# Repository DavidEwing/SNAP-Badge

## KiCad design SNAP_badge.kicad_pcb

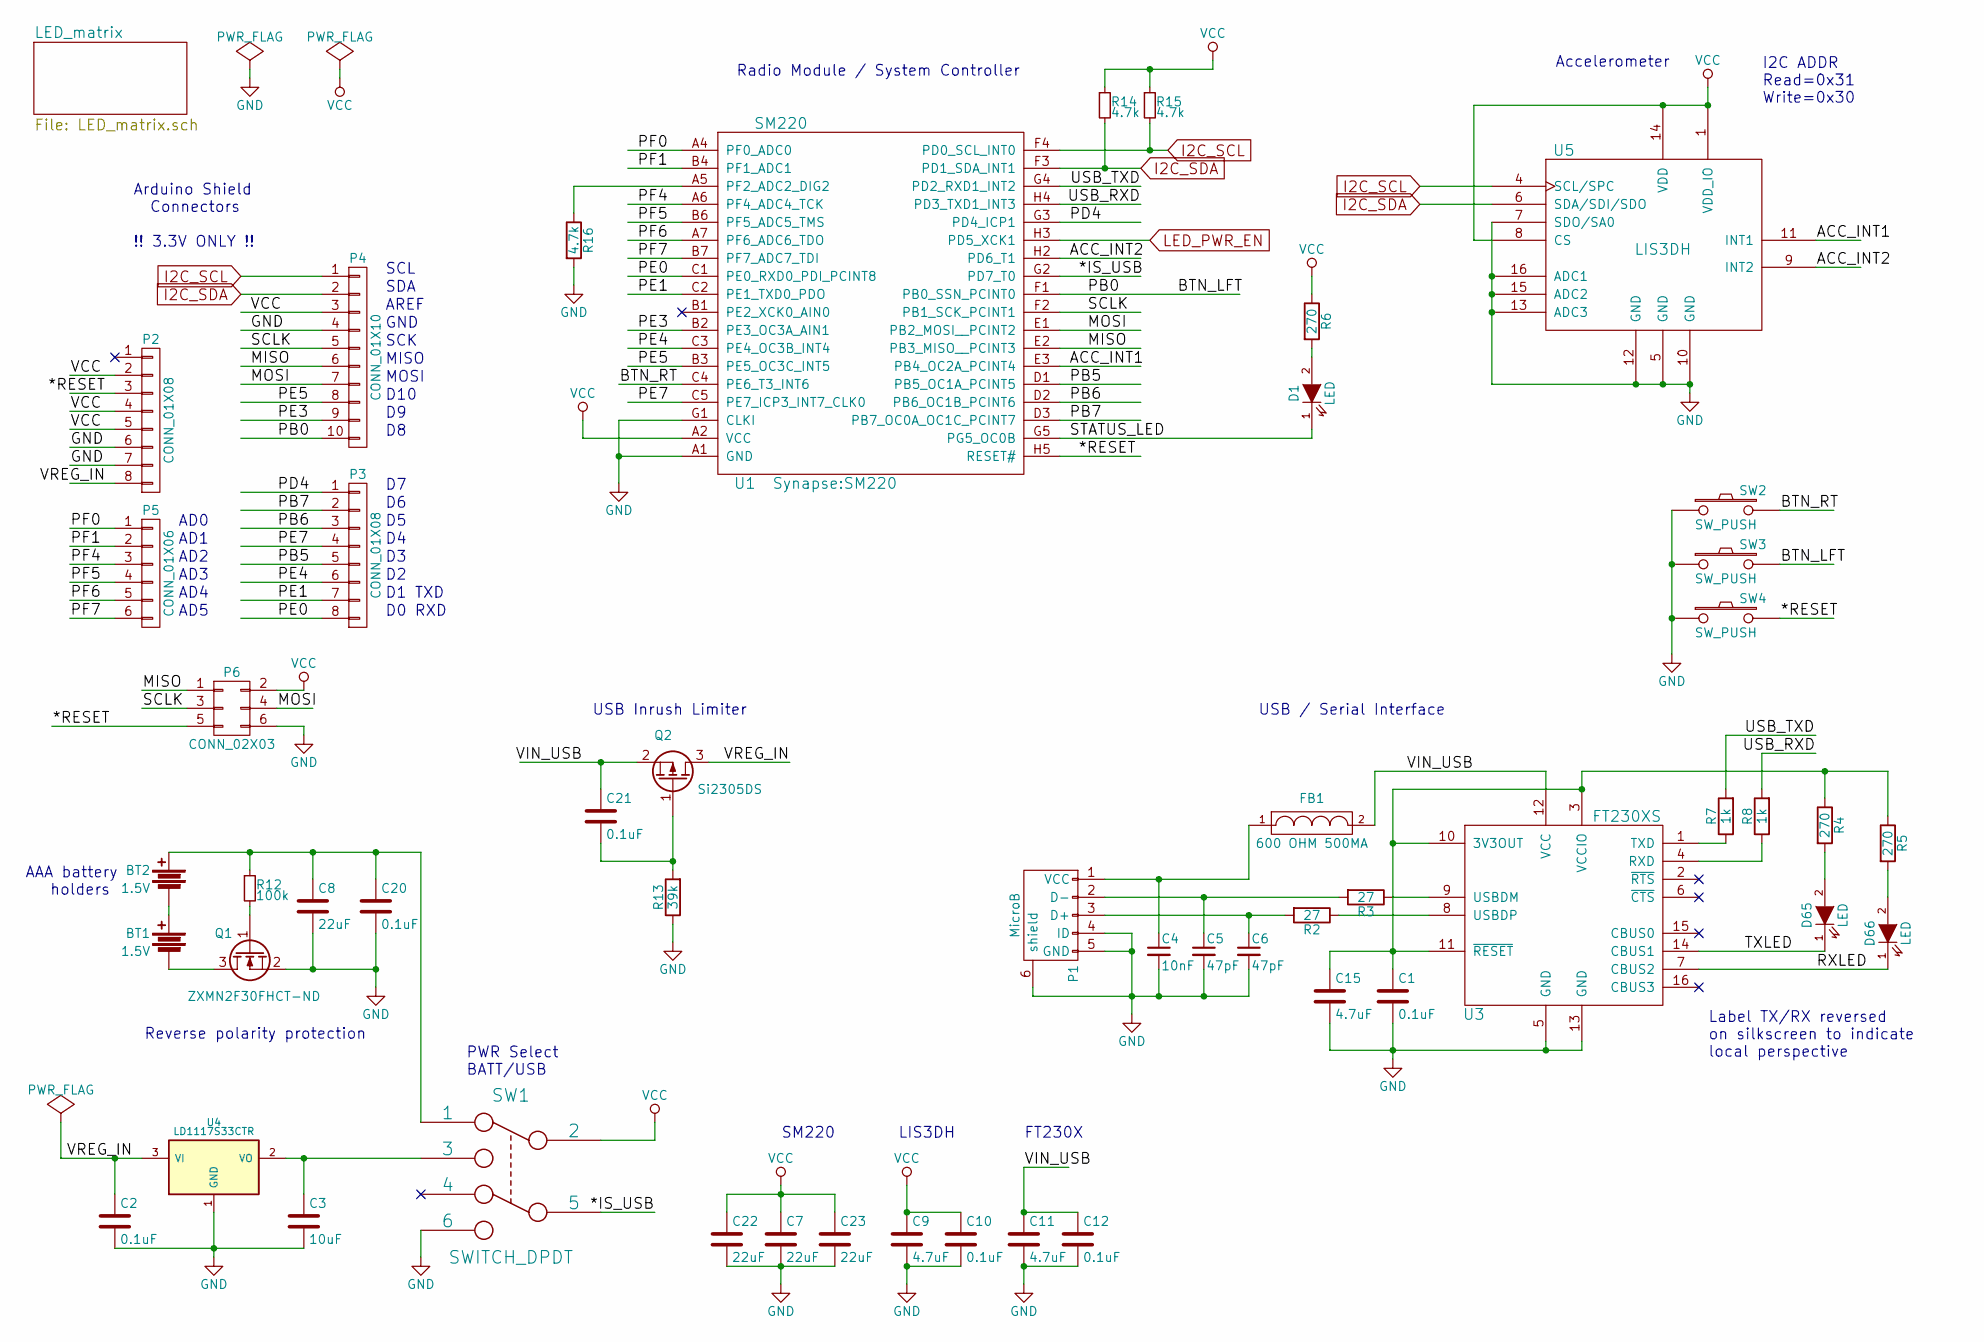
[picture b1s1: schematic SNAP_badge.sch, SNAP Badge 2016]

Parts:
BT1, BT2: 1.5V; BATT_2466
C1, C2, C10, C12, C20, C21: 0.1uF; C_0603
C3: 10uF; C_0603
C4: 10nF; C_0603
C5, C6: 47pF; C_0603
C7, C8, C22, C23: 22uF; C_0603
C9, C11, C15: 4.7uF; C_0603
D1, D65, D66: LED; Led_0603
FB1: 600 OHM 500MA; R_0603
P1: MicroB; USBmicroB
P2, P3: CONN_01X08; Socket_Strip_Straight_1x08
P4: CONN_01X10; Socket_Strip_Straight_1x10
P5: CONN_01X06; Socket_Strip_Straight_1x06
P6: CONN_02X03; Pin_Header_Straight_2x03
Q1: ZXMN2F30FHCT-ND; SOT-23
Q2: Si2305DS; SOT-23
R2, R3: 27; R_0603
R4, R5, R6: 270; R_0603
R7, R8: 1k; R_0603
R12: 100k; R_0603
R13: 39k; R_0603
R14, R15, R16: 4.7k; R_0603
SW1: SWITCH_DPDT; SO-DPDT-6
SW2, SW3, SW4: SW_PUSH; SW_SPST_PTS645
U1: SM220
U3: FT230XS; SSOP-16_3.9x4.9mm_Pitch0.635mm
U4: LD1117S33CTR; SOT-223
U5: LIS3DH; LGA16_3x3

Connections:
/*IS_USB: SW1.5, U1.G2 (PD7_T0)
/*RESET: P2.3, P6.5, SW4.2, U1.H5 (RESET#)
/ACC_INT1: U1.E3 (PB4_OC2A_PCINT4), U5.11 (INT1)
/ACC_INT2: U1.H2 (PD6_T1), U5.9 (INT2)
/BTN_LFT: P4.10, SW3.2, U1.F1 (PB0_SSN_PCINT0)
/BTN_RT: SW2.2, U1.C4 (PE6_T3_INT6)
/MISO: P4.6, P6.1, U1.E2 (PB3_MISO__PCINT3)
/MOSI: P4.7, P6.4, U1.E1 (PB2_MOSI__PCINT2)
/PB5: P3.5, U1.D1 (PB5_OC1A_PCINT5)
/PB6: P3.3, U1.D2 (PB6_OC1B_PCINT6)
/PB7: P3.2, U1.D3 (PB7_OC0A_OC1C_PCINT7)
/PD4: P3.1, U1.G3 (PD4_ICP1)
/PE0: P3.8, U1.C1 (PE0_RXD0_PDI_PCINT8)
/PE1: P3.7, U1.C2 (PE1_TXD0_PDO)
/PE3: P4.9, U1.B2 (PE3_OC3A_AIN1)
/PE4: P3.6, U1.C3 (PE4_OC3B_INT4)
/PE5: P4.8, U1.B3 (PE5_OC3C_INT5)
/PE7: P3.4, U1.C5 (PE7_ICP3_INT7_CLK0)
/PF0: P5.1, U1.A4 (PF0_ADC0)
/PF1: P5.2, U1.B4 (PF1_ADC1)
/PF4: P5.3, U1.A6 (PF4_ADC4_TCK)
/PF5: P5.4, U1.B6 (PF5_ADC5_TMS)
/PF6: P5.5, U1.A7 (PF6_ADC6_TDO)
/PF7: P5.6, U1.B7 (PF7_ADC7_TDI)
/RXLED: D66.1 (K), U3.7 (CBUS2)
/SCLK: P4.5, P6.3, U1.F2 (PB1_SCK_PCINT1)
/STATUS_LED: D1.1 (K), U1.G5 (PG5_OC0B)
/TXLED: D65.1 (K), U3.14 (CBUS1)
/USB_RXD: R8.2, U1.H4 (PD3_TXD1_INT3)
/USB_TXD: R7.2, U1.G4 (PD2_RXD1_INT2)
/VIN_USB: C11.1, C12.1, C21.1, FB1.2, Q2.2 (S), U3.12 (VCC)
/VREG_IN: C2.1, P2.8, Q2.3 (D), U4.3 (VI)
GND: C1.2, C2.2, C3.2, C4.2, C5.2, C6.2, C7.2, C8.2, C9.2, C10.2, C11.2, C12.2, C15.2, C20.2, C22.2, C23.2, P1.4 (ID), P1.5 (GND), P1.6 (shield), P2.6, P2.7, P4.4, P6.6, Q1.2 (S), R13.1, R16.2, SW1.6, SW2.1, SW3.1, SW4.1, U1.A1 (GND), U1.A8 (GND), U1.B8 (GND), U1.D8 (GND), U1.F8 (GND), U1.G1 (CLKI), U1.G8 (GND), U1.H1 (GND), U1.H8 (GND), U3.5 (GND), U3.13 (GND), U4.1 (GND), U5.5 (GND), U5.7 (SDO/SA0), U5.10 (GND), U5.12 (GND), U5.13 (ADC3), U5.15 (ADC2), U5.16 (ADC1); also elsewhere on the board
I2C_SCL: P4.1, R15.2, U1.F4 (PD0_SCL_INT0), U5.4 (SCL/SPC); also elsewhere on the board
I2C_SDA: P4.2, R14.2, U1.F3 (PD1_SDA_INT1), U5.6 (SDA/SDI/SDO); also elsewhere on the board
LED_PWR_EN: U1.H3 (PD5_XCK1); also elsewhere on the board
unnamed: BT1.1, BT2.2
unnamed: BT1.2, Q1.3 (D)
unnamed: BT2.1, C8.1, C20.1, R12.1, SW1.1
unnamed: C1.1, C15.1, R4.1, R5.1, U3.3 (VCCIO), U3.10 (3V3OUT), U3.11 (~RESET)
unnamed: C3.1, SW1.3, U4.2 (VO)
unnamed: C4.1, FB1.1, P1.1 (VCC)
unnamed: C5.1, P1.2 (D-), R3.2
unnamed: C6.1, P1.3 (D+), R2.2
unnamed: C21.2, Q2.1 (G), R13.2
unnamed: D1.2 (A), R6.2
unnamed: D65.2 (A), R4.2
unnamed: D66.2 (A), R5.2
unnamed: Q1.1 (G), R12.2
unnamed: R2.1, U3.8 (USBDP)
unnamed: R3.1, U3.9 (USBDM)
unnamed: R7.1, U3.1 (TXD)
unnamed: R8.1, U3.4 (RXD)
unnamed: R16.1, U1.A5 (PF2_ADC2_DIG2)
VCC: C7.1, C9.1, C10.1, C22.1, C23.1, P2.2, P2.4, P2.5, P4.3, P6.2, R6.1, R14.1, R15.1, SW1.2, U1.A2 (VCC), U1.A3 (VCC), U5.1 (VDD_IO), U5.8 (CS), U5.14 (VDD); also elsewhere on the board

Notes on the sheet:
Reverse polarity protection
PWR Select BATT/USB
I2C ADDR Read=0x31 Write=0x30
Accelerometer
USB / Serial Interface
Radio Module / System Controller
SM220
LIS3DH
FT230X
AD0
AD1
AD2
AD3
AD4
AD5
SCL
SDA
AREF
GND
SCK
MISO
MOSI
D10
D1 TXD
D0 RXD
Arduino Shield Connectors !! 3.3V ONLY !!
AAA battery holders
USB Inrush Limiter
Label TX/RX reversed on silkscreen to indicate local perspective

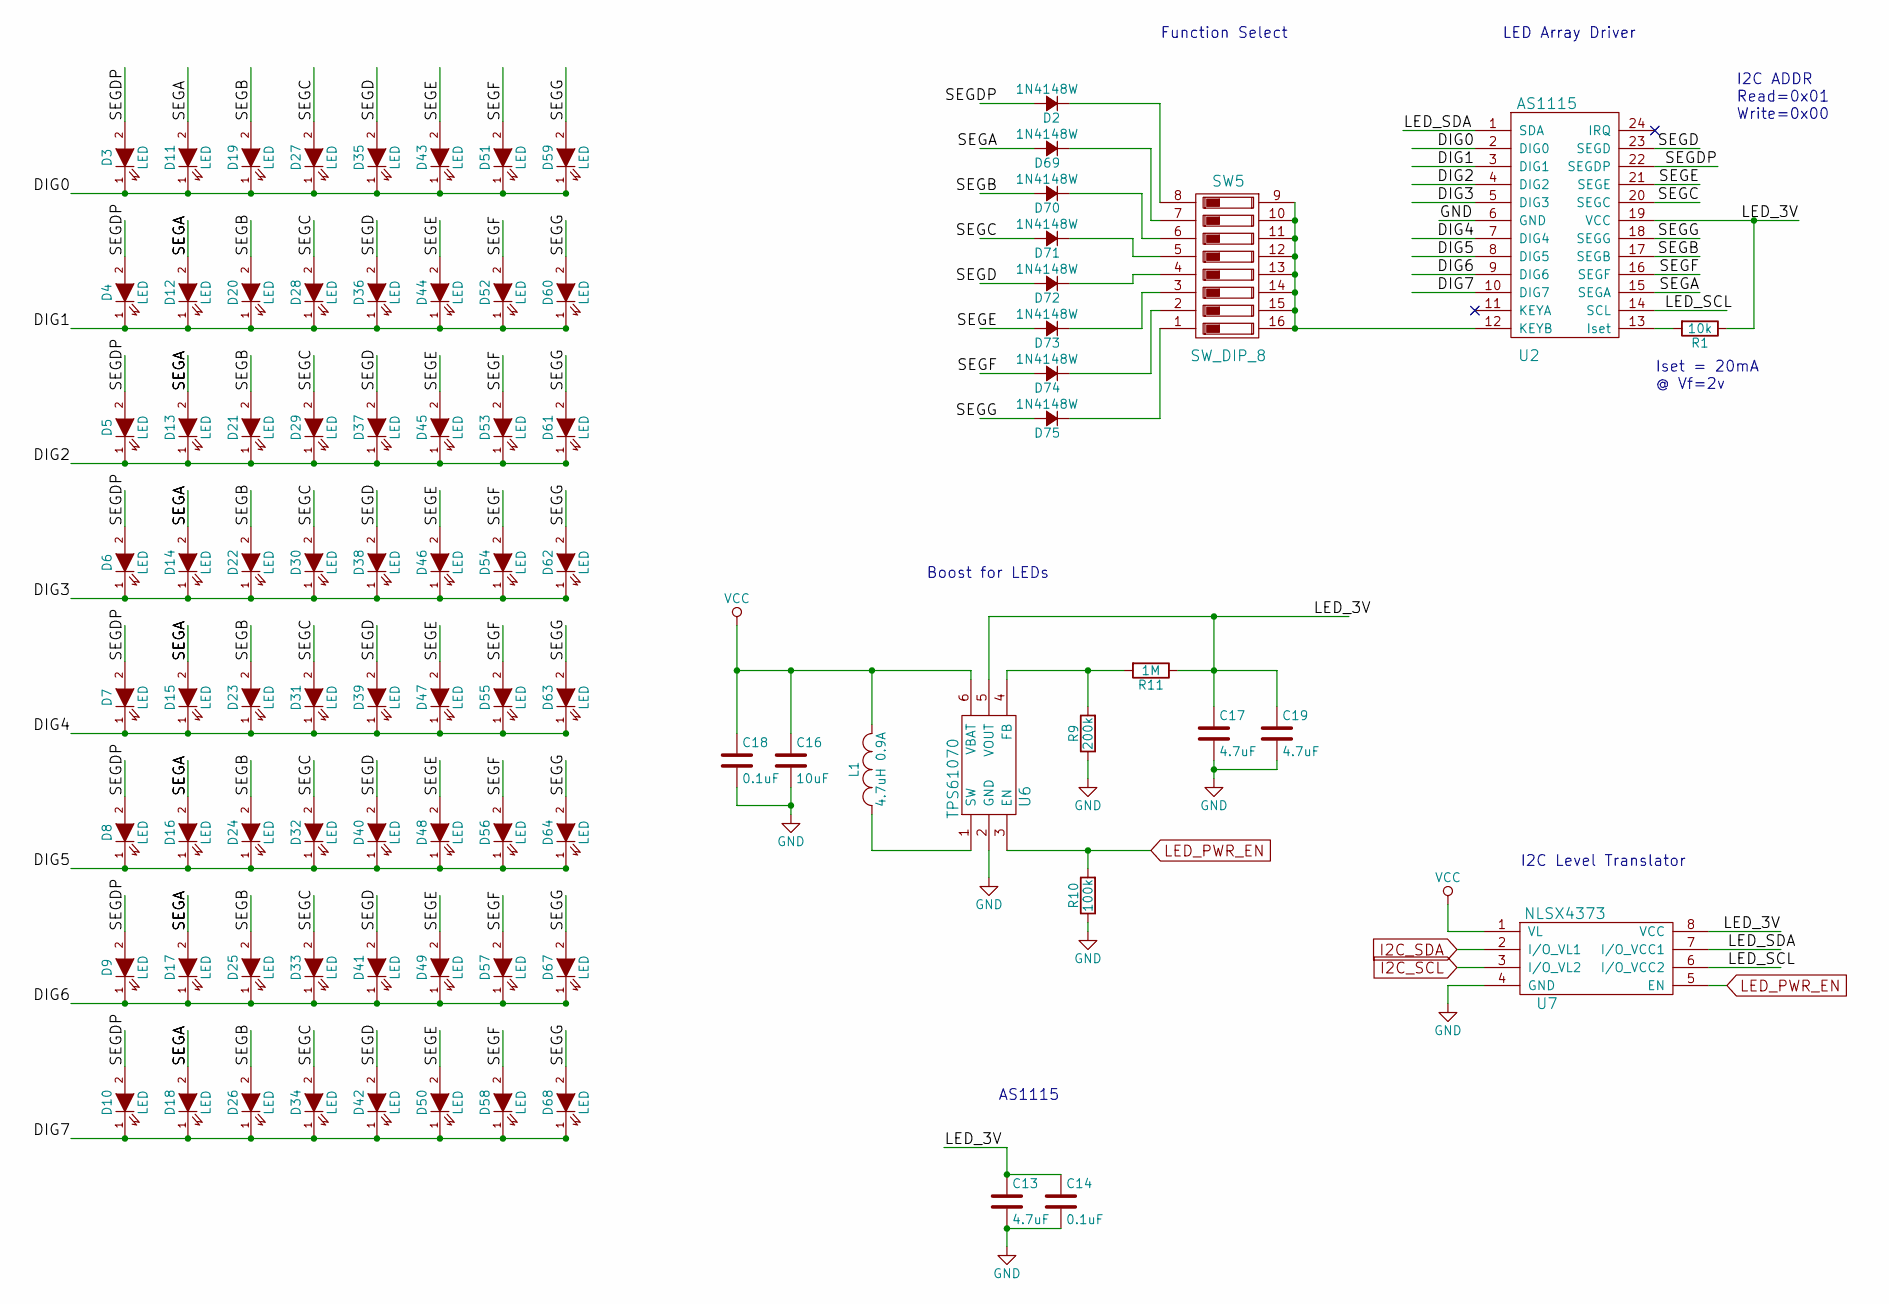
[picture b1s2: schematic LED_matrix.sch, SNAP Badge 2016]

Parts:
C13, C17, C19: 4.7uF; C_0603
C14, C18: 0.1uF; C_0603
C16: 10uF; C_0603
D2, D69, D70, D71, D72, D73, D74, D75: 1N4148W; SOD-323
D3, D4, D5, D6, D7, D8, D9, D10, D11, D12, D13, D14, D15, D16, D17, D18, D19, D20, D21, D22, D23, D24, D25, D26, D27, D28, D29, D30, D31, D32, D33, D34, D35, D36, D37, D38, D39, D40, D41, D42, D43, D44, D45, D46, D47, D48, D49, D50, D51, D52, D53, D54, D55, D56, D57, D58, D59, D60, D61, D62, D63, D64, D67, D68: LED; Led_0603
L1: 4.7uH 0.9A; TYS-2
R1: 10k; R_0603
R9: 200k; R_0603
R10: 100k; R_0603
R11: 1M; R_0603
SW5: SW_DIP_8; DIPSW-16
U2: AS1115; QSOP-24
U6: TPS61070; TSOT-6-MK06A
U7: NLSX4373; SOIC-8_3.9x4.9mm_Pitch1.27mm

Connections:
/LED_matrix/DIG0: D3.1 (K), D11.1 (K), D19.1 (K), D27.1 (K), D35.1 (K), D43.1 (K), D51.1 (K), D59.1 (K), U2.2 (DIG0)
/LED_matrix/DIG1: D4.1 (K), D12.1 (K), D20.1 (K), D28.1 (K), D36.1 (K), D44.1 (K), D52.1 (K), D60.1 (K), U2.3 (DIG1)
/LED_matrix/DIG2: D5.1 (K), D13.1 (K), D21.1 (K), D29.1 (K), D37.1 (K), D45.1 (K), D53.1 (K), D61.1 (K), U2.4 (DIG2)
/LED_matrix/DIG3: D6.1 (K), D14.1 (K), D22.1 (K), D30.1 (K), D38.1 (K), D46.1 (K), D54.1 (K), D62.1 (K), U2.5 (DIG3)
/LED_matrix/DIG4: D7.1 (K), D15.1 (K), D23.1 (K), D31.1 (K), D39.1 (K), D47.1 (K), D55.1 (K), D63.1 (K), U2.7 (DIG4)
/LED_matrix/DIG5: D8.1 (K), D16.1 (K), D24.1 (K), D32.1 (K), D40.1 (K), D48.1 (K), D56.1 (K), D64.1 (K), U2.8 (DIG5)
/LED_matrix/DIG6: D9.1 (K), D17.1 (K), D25.1 (K), D33.1 (K), D41.1 (K), D49.1 (K), D57.1 (K), D67.1 (K), U2.9 (DIG6)
/LED_matrix/DIG7: D10.1 (K), D18.1 (K), D26.1 (K), D34.1 (K), D42.1 (K), D50.1 (K), D58.1 (K), D68.1 (K), U2.10 (DIG7)
/LED_matrix/LED_3V: C13.1, C14.1, C17.1, C19.1, R1.1, R11.1, U2.19 (VCC), U6.5 (VOUT), U7.8 (VCC)
/LED_matrix/LED_SCL: U2.14 (SCL), U7.6 (I/O_VCC2)
/LED_matrix/LED_SDA: U2.1 (SDA), U7.7 (I/O_VCC1)
/LED_matrix/SEGA: D11.2 (A), D12.2 (A), D13.2 (A), D14.2 (A), D15.2 (A), D16.2 (A), D17.2 (A), D18.2 (A), D69.2 (A), U2.15 (SEGA)
/LED_matrix/SEGB: D19.2 (A), D20.2 (A), D21.2 (A), D22.2 (A), D23.2 (A), D24.2 (A), D25.2 (A), D26.2 (A), D70.2 (A), U2.17 (SEGB)
/LED_matrix/SEGC: D27.2 (A), D28.2 (A), D29.2 (A), D30.2 (A), D31.2 (A), D32.2 (A), D33.2 (A), D34.2 (A), D71.2 (A), U2.20 (SEGC)
/LED_matrix/SEGD: D35.2 (A), D36.2 (A), D37.2 (A), D38.2 (A), D39.2 (A), D40.2 (A), D41.2 (A), D42.2 (A), D72.2 (A), U2.23 (SEGD)
/LED_matrix/SEGDP: D2.2 (A), D3.2 (A), D4.2 (A), D5.2 (A), D6.2 (A), D7.2 (A), D8.2 (A), D9.2 (A), D10.2 (A), U2.22 (SEGDP)
/LED_matrix/SEGE: D43.2 (A), D44.2 (A), D45.2 (A), D46.2 (A), D47.2 (A), D48.2 (A), D49.2 (A), D50.2 (A), D73.2 (A), U2.21 (SEGE)
/LED_matrix/SEGF: D51.2 (A), D52.2 (A), D53.2 (A), D54.2 (A), D55.2 (A), D56.2 (A), D57.2 (A), D58.2 (A), D74.2 (A), U2.16 (SEGF)
/LED_matrix/SEGG: D59.2 (A), D60.2 (A), D61.2 (A), D62.2 (A), D63.2 (A), D64.2 (A), D67.2 (A), D68.2 (A), D75.2 (A), U2.18 (SEGG)
GND: C13.2, C14.2, C16.2, C17.2, C18.2, C19.2, R9.1, R10.1, U2.6 (GND), U6.2 (GND), U7.4 (GND); also elsewhere on the board
I2C_SCL: U7.3 (I/O_VL2); also elsewhere on the board
I2C_SDA: U7.2 (I/O_VL1); also elsewhere on the board
LED_PWR_EN: R10.2, U6.3 (EN), U7.5 (EN); also elsewhere on the board
unnamed: D2.1 (K), SW5.8
unnamed: D69.1 (K), SW5.7
unnamed: D70.1 (K), SW5.6
unnamed: D71.1 (K), SW5.5
unnamed: D72.1 (K), SW5.4
unnamed: D73.1 (K), SW5.3
unnamed: D74.1 (K), SW5.2
unnamed: D75.1 (K), SW5.1
unnamed: L1.1, U6.1 (SW)
unnamed: R1.2, U2.13 (Iset)
unnamed: R9.2, R11.2, U6.4 (FB)
unnamed: SW5.9, SW5.10, SW5.11, SW5.12, SW5.13, SW5.14, SW5.15, SW5.16, U2.12 (KEYB)
VCC: C16.1, C18.1, L1.2, U6.6 (VBAT), U7.1 (VL); also elsewhere on the board

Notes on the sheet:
AS1115
Boost for LEDs
LED Array Driver
Function Select
I2C ADDR Read=0x01 Write=0x00
Iset = 20mA @ Vf=2v
I2C Level Translator

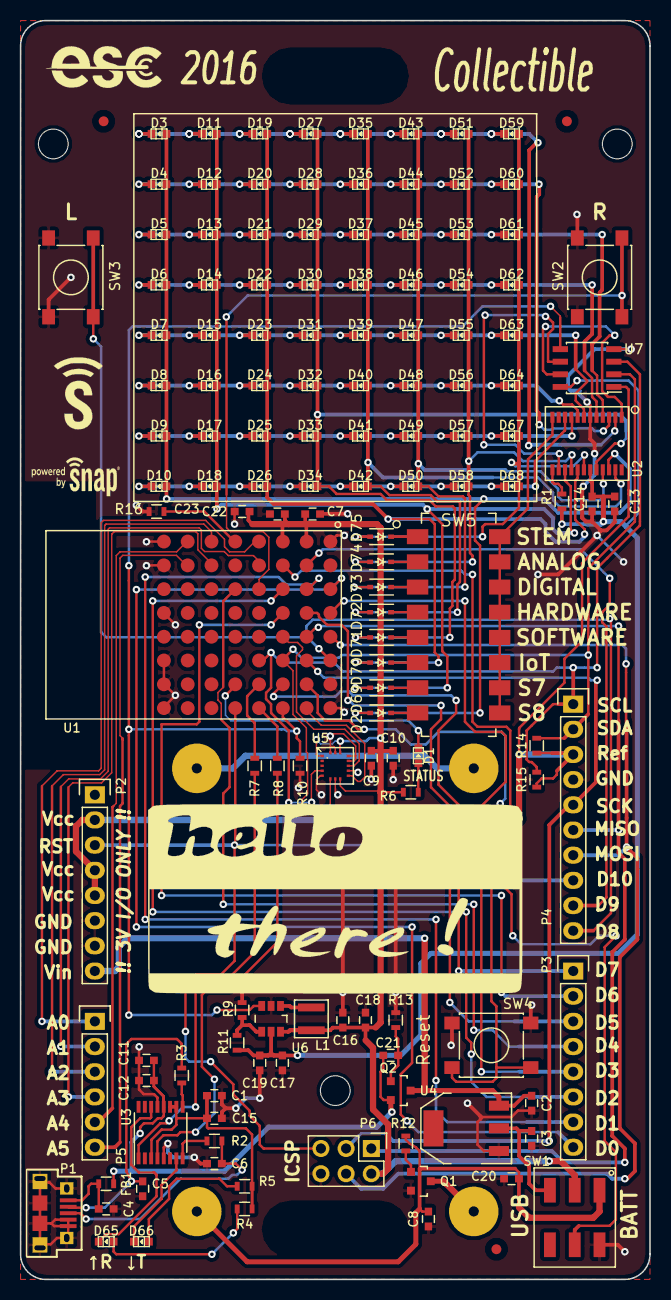
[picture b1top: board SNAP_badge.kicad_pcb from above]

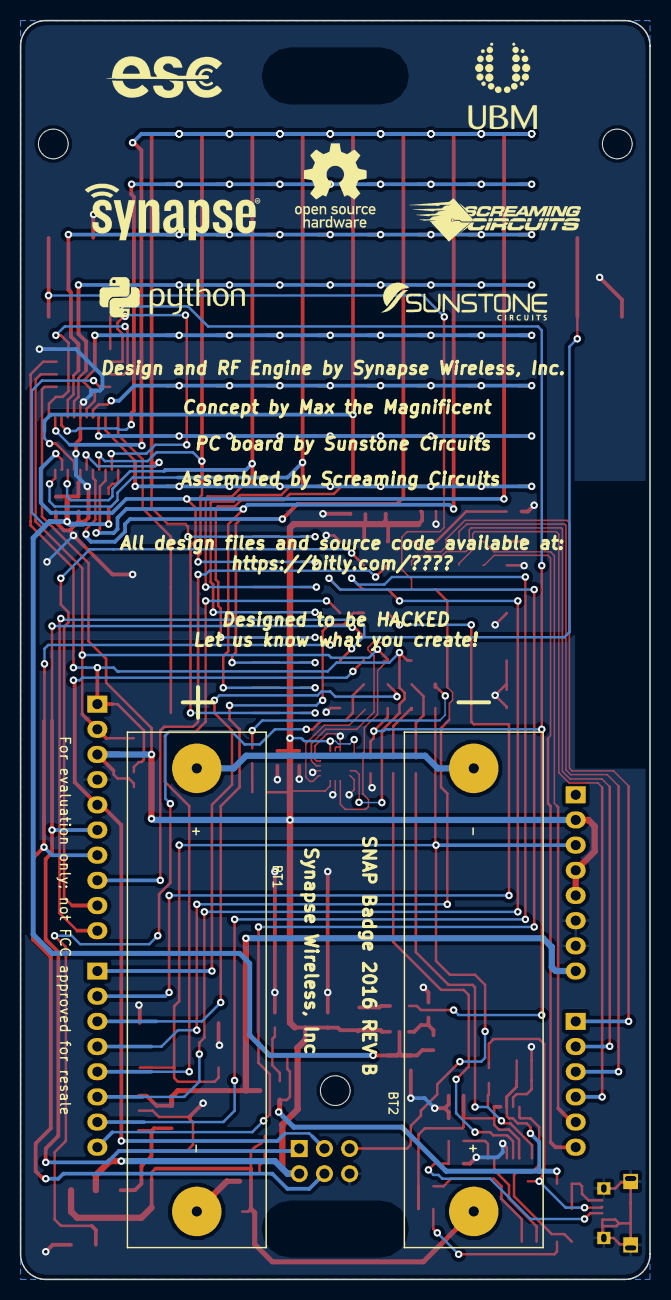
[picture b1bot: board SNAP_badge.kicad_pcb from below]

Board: 2 copper layers, 63.5 x 127.0 mm, 141 parts (2 on the bottom side), 86 nets.

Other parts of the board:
Fiducial_Mark: VAL**; Fiducial_Mark
Fiducial_Mark#2, Fiducial_Mark#3: VAL**; Fiducial_Mark

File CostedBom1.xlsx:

Source | D:/HardwareDev/test_board2/test_board2.sch
Kicad Rev | Eeschema 4.0.0-rc2-stable
Generated Date | 42341.483796296299
Title | SNAP Badge 2016
Company | Synapse Wireless
Revision | A
Date Issue | 42339
Reference | Value | Kcost | PN | Library | Library Ref |  | Pads THT | Pads SMT | Pads NL
U3 | FT230XS | 1.53 | FT230XS-R | FT230XS | FT230XS |  |  | 24
FB1 | 600 OHM 500MA | 0.1 | FILTER |  |  |  |  | 2
R3 | 27 | 0.01 | R |  |  |  |  | 2
R2 | 27 | 0.01 | R |  |  |  |  | 2
C1 | 100nF | 0.01 | C |  |  |  |  | 2
D65 | LED | 0.03 | LED |  |  |  |  | 2
D66 | LED | 0.03 | LED |  |  |  |  | 2
R4 | 270 | 0.01 | R |  |  |  |  | 2
R5 | 270 | 0.01 | R |  |  |  |  | 2
U4 | LD1117S33CTR | 0.14000000000000001 |  | regul | LD1117S33CTR |  |  | 3
C2 | 100nF | 0.01 | C |  |  |  |  | 2
BT1 | 1.5V | 0.2 | Battery |  |  |  | 2
SW1 | SWITCH_DPDT | 0.26 | JS202011SCQN | SWITCH_DPDT | SWITCH_DPDT |  |  | 6
C4 | 10nF | 0.01 | C_Small |  |  |  |  | 2
C5 | 47pF | 0.01 | C_Small |  |  |  |  | 2
C6 | 47pF | 0.01 | C_Small |  |  |  |  | 2
BT2 | 1.5V | 0.2 | Battery |  |  |  | 2
U5 | LIS3DH | 0.8 | LIS3DHTR | STM_MEMS | LIS3DH |  |  |  | 16
C3 | 10uF | 0.01 | C |  |  |  |  | 2
C7 | 22uF | 0.01 | C |  |  |  |  | 2
C9 | 4.7uF | 0.01 | C |  |  |  |  | 2
C10 | 0.1uF | 0.01 | C |  |  |  |  | 2
C11 | 4.7uF | 0.01 | C |  |  |  |  | 2
C12 | 0.1uF | 0.01 | C |  |  |  |  | 2
SW2 | SW_PUSH | 0.16 | PTS645SL50SMTR92 LFS | device | SW_PUSH |  |  | 2
D1 | LED | 0.03 | LED |  |  |  |  | 2
R6 | 270 | 0.01 | R |  |  |  |  | 2
P2 | CONN_01X08 | 0 | CONN_01X08
P3 | CONN_01X08 | 0 | CONN_01X08
P4 | CONN_01X10 | 0 | CONN_01X10
P5 | CONN_01X06 | 0 | CONN_01X06
P6 | CONN_02X03 | 0 | CONN_02X03
U1 | SM220 | 0 | SM220 |  |  |  |  |  | 64
R7 | 1k | 0.01 | R |  |  |  |  | 2
R8 | 1k | 0.01 | R |  |  |  |  | 2
C15 | 4.7uF | 0.01 | C |  |  |  |  | 2
R12 | 100k | 0.01 | R_Small |  |  |  |  | 2
C8 | 22uF | 0.01 | C |  |  |  |  | 2
C20 | 0.1uF | 0.01 | C |  |  |  |  | 2
Q2 | Si2305DS | 0.14000000000000001 | Q_PMOS_GSD |  |  |  |  | 3
C21 | 100nF | 0.01 | C |  |  |  |  | 2
R13 | 39k | 0.01 | R |  |  |  |  | 2
Q1 | ZXMN2F30FHCT-ND | 0.15 | Q_NMOS_GSD |  |  |  |  | 3
C23 | 22uF | 0.01 | C |  |  |  |  | 2
C22 | 22uF | 0.01 | C |  |  |  |  | 2
R14 | 4.7k | 0.01 | R_Small |  |  |  |  | 2
R15 | 4.7k | 0.01 | R_Small |  |  |  |  | 2
SW3 | SW_PUSH | 0.16 | PTS645SL50SMTR92 LFS | device | SW_PUSH |  |  | 2
SW4 | SW_PUSH | 0.16 | PTS645SL50SMTR92 LFS | device | SW_PUSH |  |  | 2
P1 | MicroB | 0.2 | USB_OTG |  |  |  | 4 | 5
D11 | LED | 0.03 | LED |  |  |  |  | 2
D19 | LED | 0.03 | LED |  |  |  |  | 2
D27 | LED | 0.03 | LED |  |  |  |  | 2
D35 | LED | 0.03 | LED |  |  |  |  | 2
D43 | LED | 0.03 | LED |  |  |  |  | 2
D51 | LED | 0.03 | LED |  |  |  |  | 2
D59 | LED | 0.03 | LED |  |  |  |  | 2
D3 | LED | 0.03 | LED |  |  |  |  | 2
D12 | LED | 0.03 | LED |  |  |  |  | 2
D20 | LED | 0.03 | LED |  |  |  |  | 2
D28 | LED | 0.03 | LED |  |  |  |  | 2
D36 | LED | 0.03 | LED |  |  |  |  | 2
D44 | LED | 0.03 | LED |  |  |  |  | 2
D52 | LED | 0.03 | LED |  |  |  |  | 2
D60 | LED | 0.03 | LED |  |  |  |  | 2
D4 | LED | 0.03 | LED |  |  |  |  | 2
D13 | LED | 0.03 | LED |  |  |  |  | 2
D21 | LED | 0.03 | LED |  |  |  |  | 2
D29 | LED | 0.03 | LED |  |  |  |  | 2
D37 | LED | 0.03 | LED |  |  |  |  | 2
D45 | LED | 0.03 | LED |  |  |  |  | 2
D53 | LED | 0.03 | LED |  |  |  |  | 2
D61 | LED | 0.03 | LED |  |  |  |  | 2
D5 | LED | 0.03 | LED |  |  |  |  | 2
D14 | LED | 0.03 | LED |  |  |  |  | 2
D22 | LED | 0.03 | LED |  |  |  |  | 2
D30 | LED | 0.03 | LED |  |  |  |  | 2
D38 | LED | 0.03 | LED |  |  |  |  | 2
D46 | LED | 0.03 | LED |  |  |  |  | 2
D54 | LED | 0.03 | LED |  |  |  |  | 2
D62 | LED | 0.03 | LED |  |  |  |  | 2
D6 | LED | 0.03 | LED |  |  |  |  | 2
D15 | LED | 0.03 | LED |  |  |  |  | 2
D23 | LED | 0.03 | LED |  |  |  |  | 2
D31 | LED | 0.03 | LED |  |  |  |  | 2
D39 | LED | 0.03 | LED |  |  |  |  | 2
D47 | LED | 0.03 | LED |  |  |  |  | 2
D55 | LED | 0.03 | LED |  |  |  |  | 2
D63 | LED | 0.03 | LED |  |  |  |  | 2
D7 | LED | 0.03 | LED |  |  |  |  | 2
D16 | LED | 0.03 | LED |  |  |  |  | 2
D24 | LED | 0.03 | LED |  |  |  |  | 2
D32 | LED | 0.03 | LED |  |  |  |  | 2
D40 | LED | 0.03 | LED |  |  |  |  | 2
D48 | LED | 0.03 | LED |  |  |  |  | 2
D56 | LED | 0.03 | LED |  |  |  |  | 2
D64 | LED | 0.03 | LED |  |  |  |  | 2
D8 | LED | 0.03 | LED |  |  |  |  | 2
D17 | LED | 0.03 | LED |  |  |  |  | 2
D25 | LED | 0.03 | LED |  |  |  |  | 2
D33 | LED | 0.03 | LED |  |  |  |  | 2
D41 | LED | 0.03 | LED |  |  |  |  | 2
D49 | LED | 0.03 | LED |  |  |  |  | 2
D57 | LED | 0.03 | LED |  |  |  |  | 2
D67 | LED | 0.03 | LED |  |  |  |  | 2
D9 | LED | 0.03 | LED |  |  |  |  | 2
D18 | LED | 0.03 | LED |  |  |  |  | 2
D26 | LED | 0.03 | LED |  |  |  |  | 2
D34 | LED | 0.03 | LED |  |  |  |  | 2
D42 | LED | 0.03 | LED |  |  |  |  | 2
D50 | LED | 0.03 | LED |  |  |  |  | 2
D58 | LED | 0.03 | LED |  |  |  |  | 2
D68 | LED | 0.03 | LED |  |  |  |  | 2
D10 | LED | 0.03 | LED |  |  |  |  | 2
R1 | 10k | 0.01 | R |  |  |  |  | 2
C13 | 4.7uF | 0.01 | C |  |  |  |  | 2
C14 | 0.1uF | 0.01 | C |  |  |  |  | 2
U2 | AS1115 | 2.11 | AS1115-BSST | as111x | AS1115 |  |  | 24
D2 | 1N4148W | 0.03 | 1N4148W-7-F | device | D_Small |  |  | 2
SW5 | SW_DIP_8 | 0.58599999999999997 | 1-1825058-9 | sw_dip | SW_DIP_8 |  |  | 16
L1 | 4.7uH 0.9A | 0.18 | TYS30124R7M-10 | device | INDUCTOR_SMALL |  |  | 2
U6 | TPS61070 | 0.5 | TPS61070DDCR | regulators | TPS61070 |  |  | 6
R11 | 1M | 0.01 | R |  |  |  |  | 2
R9 | 200k | 0.01 | R |  |  |  |  | 2
R10 | 100k | 0.01 | R |  |  |  |  | 2
C16 | 10uF | 0.01 | C |  |  |  |  | 2
C17 | 4.7uF | 0.01 | C |  |  |  |  | 2
C18 | 100nF | 0.01 | C |  |  |  |  | 2
C19 | 4.7uF | 0.01 | C |  |  |  |  | 2
D69 | 1N4148W | 0.03 | 1N4148W-7-F | device | D_Small |  |  | 2
D70 | 1N4148W | 0.03 | 1N4148W-7-F | device | D_Small |  |  | 2
D71 | 1N4148W | 0.03 | 1N4148W-7-F | device | D_Small |  |  | 2
D72 | 1N4148W | 0.03 | 1N4148W-7-F | device | D_Small |  |  | 2
D73 | 1N4148W | 0.03 | 1N4148W-7-F | device | D_Small |  |  | 2
D74 | 1N4148W | 0.03 | 1N4148W-7-F | device | D_Small |  |  | 2
D75 | 1N4148W | 0.03 | 1N4148W-7-F | device | D_Small |  |  | 2
U7 | NLSX4373 | 0.4 | NLSX4373 | nlsx4373 | NLSX4373 |  |  | 8
 |  |  |  |  |  |  | THT | SMT | NL |  |  | manual | manual+st | auto
 | BOM | 10.606000000000005 |  |  |  |  | 8 | 334 | 80 |  |  | 41.529989999999998 | 17.639989999999997 | 5.2399899999999997
 |  |  |  |  |  |  | 87 | 86 | 33 |  |  | 17.17999 | 9.9199900000000003 | 6.2399900000000006
 | Est PCB | 2
 | Est Assy | 6
 | Est Test | 2
 | Batteries | 0.5

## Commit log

2015-12-02 After 1st design review
2015-12-02 Arduino footprint laid out
2015-12-05 First placement
2015-12-07 Placement v1
2015-12-08 Backup
2015-12-10 Placement complete.
2015-12-12 LEDs routed
2015-12-15 Routing complete
2015-12-15 Routing complete, first check. Prior to GND fill.
2015-12-15 Finished ground pours, all DRC passing
2015-12-16 Cleanup, first gerber gen
2015-12-17 First version sent to CM for review (Screaming Circuits)
2015-12-18 Update sch with Mfg and PN fields, added Screaming Circuits to silk.
2015-12-21 Beginning cleanup - rename badge project files
2015-12-21 Change to refactored Kicad local libraries
2015-12-21 Rename gerbers
2015-12-21 BOM update
2015-12-21 Generated gerbers after library reorg
2015-12-22 Added 'INSERT' (aka SMD) property to footprints, so they appear in placement (.pos) file. Added .pos file.
2015-12-22 Rename docs for consistency
2015-12-22 Track gerber zip sent to CM
2015-12-22 Updated QSOP24 footprint 3D model scale (TSSOP/QSOP ratio)
2016-02-09 Fixed LED silkscreen, added logos
2016-02-18 Update silkscreen with logos, etc.
2016-02-18 Generated docs
2016-02-18 Updated version to RevB
